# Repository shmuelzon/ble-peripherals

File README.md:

# BLE Peripherals

:exclamation:**Warning**:exclamation: I'm not an EE by any means and I have no
idea what I'm doing! These designs are for reference only and should not be
used.

If you are an EE or am knowledgeable enough to fix my mistakes, a pull
request would be most welcome.

Now that that's out of the way, this repository includes the hardware for
various BLE-based sensors and actuators. Each directory includes a schematic,
PCB layout and a plastic enclosure design for a BLE peripheral.

The software for these designs can be found in my
[cc2640-home-automation](https://github.com/shmuelzon/cc2640-home-automation)
repository.

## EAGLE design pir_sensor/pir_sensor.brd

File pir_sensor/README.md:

# PIR Sensor

This peripheral is a multi-sensor device including a PIR motion sensor, ambient
light sensor, ambient temperature sensor, relative humidity sensor and pressure
sensor.  It also in includes an LED that will turn on when motion was detected.
Depending on the kind of traffic expected where this device will be placed,
consider disabling the LED to conserve battery power.

Battery Type: 1/2 AA (ER14250)

Board configuration for
[cc2640-home-automation](https://github.com/shmuelzon/cc2640-home-automation):
```c
#define Board_LED1                          IOID_4
#define Board_I2C0_SDA0                     IOID_7
#define Board_I2C0_SCL0                     IOID_8
#define Board_MOTION                        IOID_5
#define Board_OPT3001_ADDR                  (0x45)
#define Board_BME280_ADDR                   (0x77)
#define Board_BATT_MAX                      3600
#define Board_BATT_MIN                      1800
```

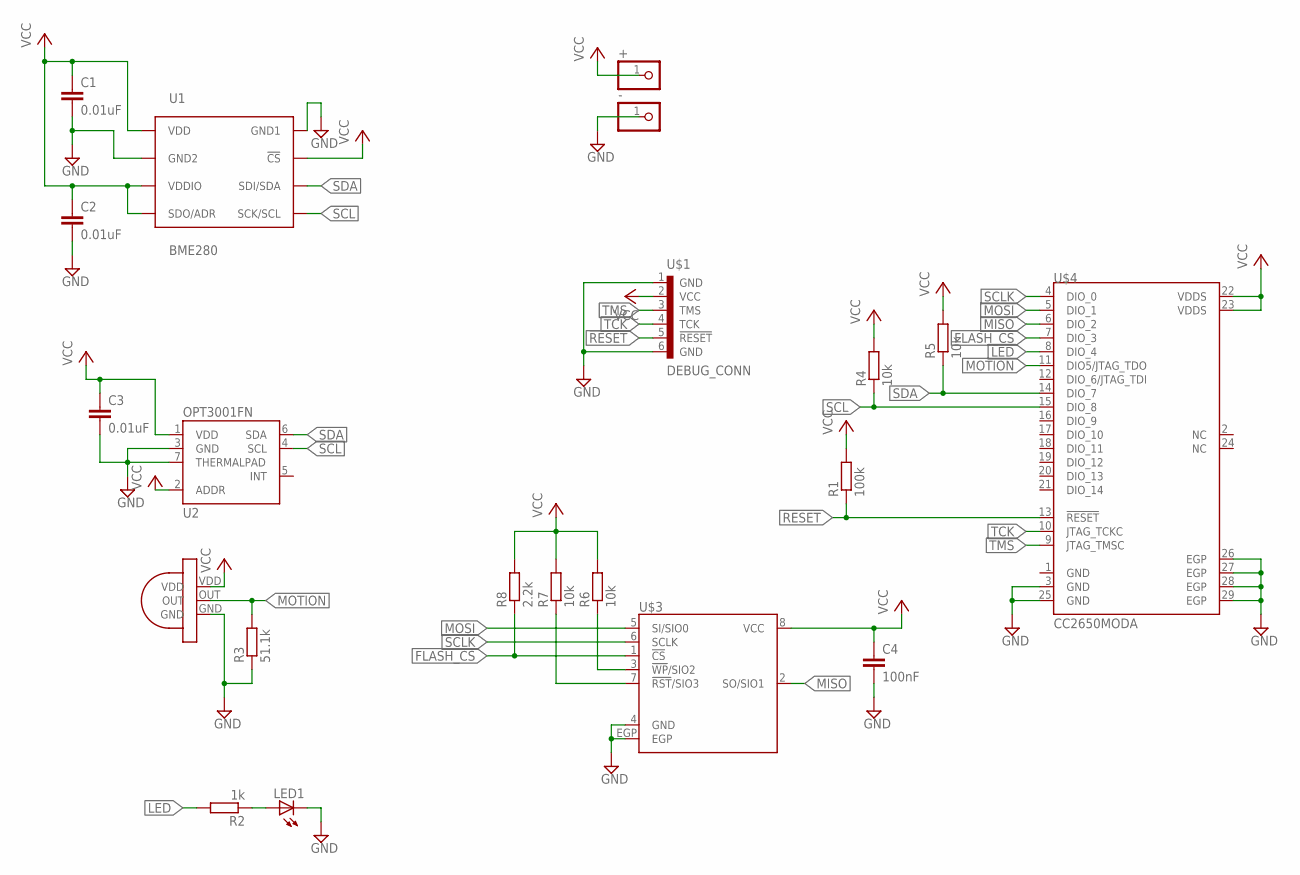
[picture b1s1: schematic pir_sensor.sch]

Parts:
+: PINHD-1X1; 1X01
-: PINHD-1X1; 1X01
C1, C2, C3: 0.01uF; 0402
C4: 100nF; 0402
LED1: LEDCHIP-LED0603; CHIP-LED0603
R1: 100k; 0402
R2: 1k; 0402
R3: 51.1k; 0402
R4, R5, R6, R7: 10k; 0402
R8: 2.2k; 0402
U1: BME280; BME280_LGA
U2: OPT3001FN; TI-USON6-GND-PAD
U$1: DEBUG_CONN
U$2: PAPIR
U$3: MX25R8035FMX25R8035FZUIL0; MX25R8035FZUIL0
U$4: CC2650MODA

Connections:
!RESET: R1.1, U$1.5 (!RESET), U$4.13 (!RESET)
FLASH_CS: R8.1, U$3.1 (!CS), U$4.7 (DIO_3)
GND: -.1, C1.2, C2.2, C3.2, C4.2, LED1.C, R3.1, U1.P$1 (GND1), U1.P$7 (GND2), U2.3 (GND), U2.7 (THERMALPAD), U$1.1 (GND), U$1.6 (GND), U$2.GND, U$3.4 (GND), U$3.EGP, U$4.1 (GND), U$4.3 (GND), U$4.25 (GND), U$4.26 (EGP), U$4.27 (EGP), U$4.28 (EGP), U$4.29 (EGP)
LED: R2.2, U$4.8 (DIO_4)
MISO: U$3.2 (SO/SIO1), U$4.6 (DIO_2)
MOSI: U$3.5 (SI/SIO0), U$4.5 (DIO_1)
MOTION: R3.2, U$2.OUT, U$4.11 (DIO5/JTAG_TDO)
unnamed: R6.1, U$3.3 (!WP!/SIO2)
unnamed: R7.1, U$3.7 (!RST!/SIO3)
unnamed: LED1.A, R2.1
SCL: R4.1, U1.P$4 (SCK/SCL), U2.4 (SCL), U$4.15 (DIO_8)
SCLK: U$3.6 (SCLK), U$4.4 (DIO_0)
SDA: R5.1, U1.P$3 (SDI/SDA), U2.6 (SDA), U$4.14 (DIO_7)
TCK: U$1.4 (TCK), U$4.10 (JTAG_TCKC)
TMS: U$1.3 (TMS), U$4.9 (JTAG_TMSC)
VCC: +.1, C1.1, C2.1, C3.1, C4.1, R1.2, R4.2, R5.2, R6.2, R7.2, R8.2, U1.P$2 (!CS), U1.P$5 (SDO/ADR), U1.P$6 (VDDIO), U1.P$8 (VDD), U2.1 (VDD), U2.2 (ADDR), U$1.2 (VCC), U$2.VDD, U$3.8 (VCC), U$4.22 (VDDS), U$4.23 (VDDS)

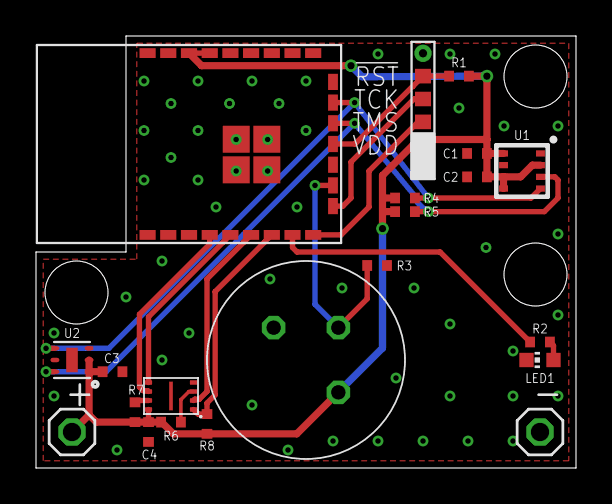
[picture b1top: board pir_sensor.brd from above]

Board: 2 copper layers, 30.0 x 24.0 mm, 21 parts (0 on the bottom side), 16 nets.

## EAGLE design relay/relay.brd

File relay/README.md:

# Relay

This peripheral is a relay with switch sensor. It's to be placed behind the wall
switch where the live wires should be connected to the inner terminals of the
blue block and additional wires should be connected to the green terminals and
the physical switch.

Toggling the switch will toggle the relay.

Battery Type: CR2

Board configuration for
[cc2640-home-automation](https://github.com/shmuelzon/cc2640-home-automation):
```c
#define Board_SWITCH                        IOID_5
#define Board_RELAY_SET                     IOID_7
#define Board_RELAY_RESET                   IOID_8
#define Board_BATT_MAX                      3000
#define Board_BATT_MIN                      2100
```

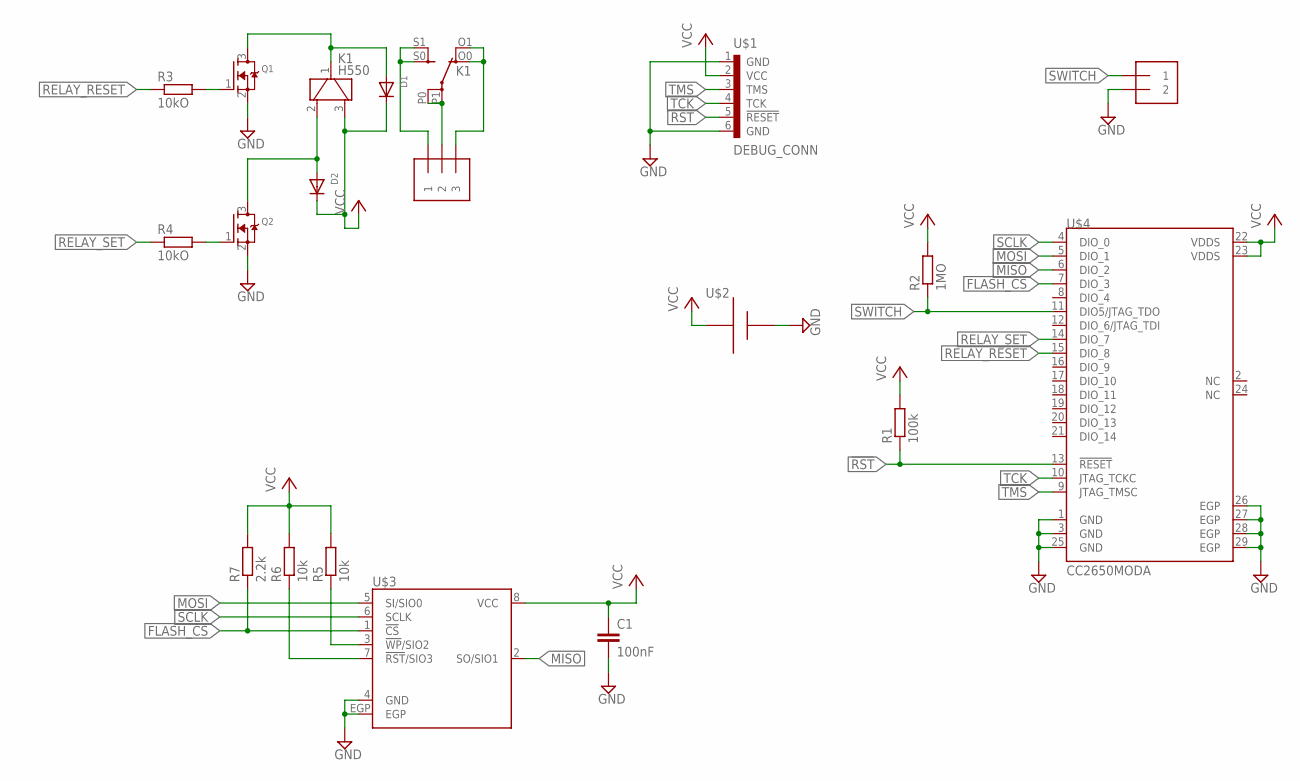
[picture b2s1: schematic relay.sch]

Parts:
C1: 100nF; 0402
D1, D2: DIODESOD-123; SOD-123
J1: 1X3-5MM
J2: 1X2-3.5MM
K1: H550
Q1, Q2: MOSFET-NREFLOW; SOT23
R1: 100k; 0402
R2: 1MO; 0402
R3, R4: 10kO; 0402
R5, R6: 10k; 0402
R7: 2.2k; 0402
U$1: DEBUG_CONN
U$2: CR2_SPRINGS; CR2
U$3: MX25R8035FMX25R8035FZUIL0; MX25R8035FZUIL0
U$4: CC2650MODA

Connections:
!RST: R1.1, U$1.5 (!RESET), U$4.13 (!RESET)
FLASH_CS: R7.1, U$3.1 (!CS), U$4.7 (DIO_3)
GND: C1.2, J2.2, Q1.2 (S), Q2.2 (S), U$1.1 (GND), U$1.6 (GND), U$2.-, U$2.-@1 (-), U$2.-@2 (-), U$2.-@3 (-), U$3.4 (GND), U$3.EGP, U$4.1 (GND), U$4.3 (GND), U$4.25 (GND), U$4.26 (EGP), U$4.27 (EGP), U$4.28 (EGP), U$4.29 (EGP)
MISO: U$3.2 (SO/SIO1), U$4.6 (DIO_2)
MOSI: U$3.5 (SI/SIO0), U$4.5 (DIO_1)
unnamed: J1.1, K1.S0 (S), K1.S1 (S)
unnamed: J1.3, K1.O0 (O), K1.O1 (O)
unnamed: D1.A, K1.1, Q1.3 (D)
unnamed: D2.A, K1.2, Q2.3 (D)
unnamed: Q1.1 (G), R3.2
unnamed: Q2.1 (G), R4.2
unnamed: J1.2, K1.P0, K1.P1
unnamed: R5.1, U$3.3 (!WP!/SIO2)
unnamed: R6.1, U$3.7 (!RST!/SIO3)
RELAY_RESET: R3.1, U$4.15 (DIO_8)
RELAY_SET: R4.1, U$4.14 (DIO_7)
SCLK: U$3.6 (SCLK), U$4.4 (DIO_0)
SWITCH: J2.1, R2.1, U$4.11 (DIO5/JTAG_TDO)
TCK: U$1.4 (TCK), U$4.10 (JTAG_TCKC)
TMS: U$1.3 (TMS), U$4.9 (JTAG_TMSC)
VCC: C1.1, D1.C, D2.C, K1.3, R1.2, R2.2, R5.2, R6.2, R7.2, U$1.2 (VCC), U$2.+, U$2.+@1 (+), U$2.+@2 (+), U$2.+@3 (+), U$3.8 (VCC), U$4.22 (VDDS), U$4.23 (VDDS)

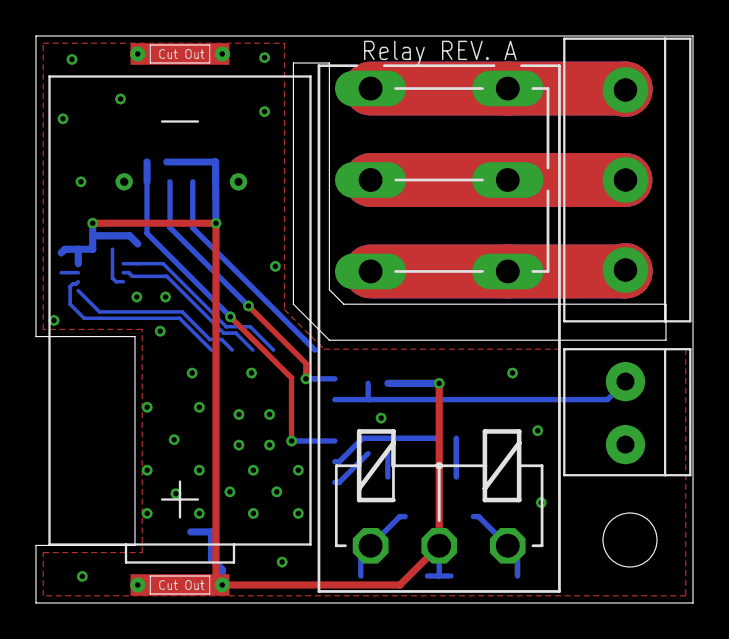
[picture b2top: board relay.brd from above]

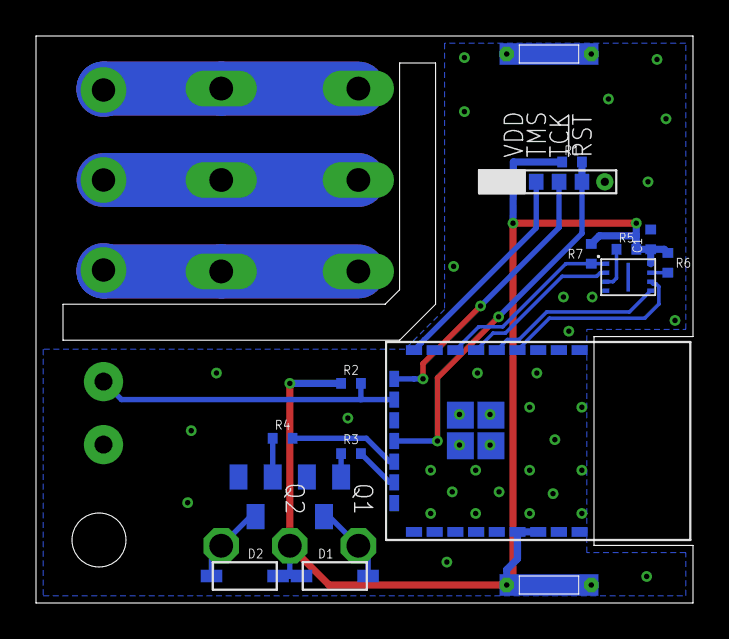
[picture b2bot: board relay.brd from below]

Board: 2 copper layers, 36.5 x 31.5 mm, 19 parts (15 on the bottom side), 21 nets.

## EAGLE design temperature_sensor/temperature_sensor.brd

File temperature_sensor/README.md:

# Temperature Sensor

This peripheral is a temperature sensor based on a thermistor. It can be used to
measure the temperature at various locations, e.g. the thermostat of a water
heater / boiler.

Battery Type: 1/2 AA (ER14250)

Board configuration for
[cc2640-home-automation](https://github.com/shmuelzon/cc2640-home-automation):
```c
#define Board_THERMISTOR_POWER              IOID_0
#define Board_THERMISTOR                    Board_ADC7
#define Board_BATT_MAX                      3600
#define Board_BATT_MIN                      1800
```

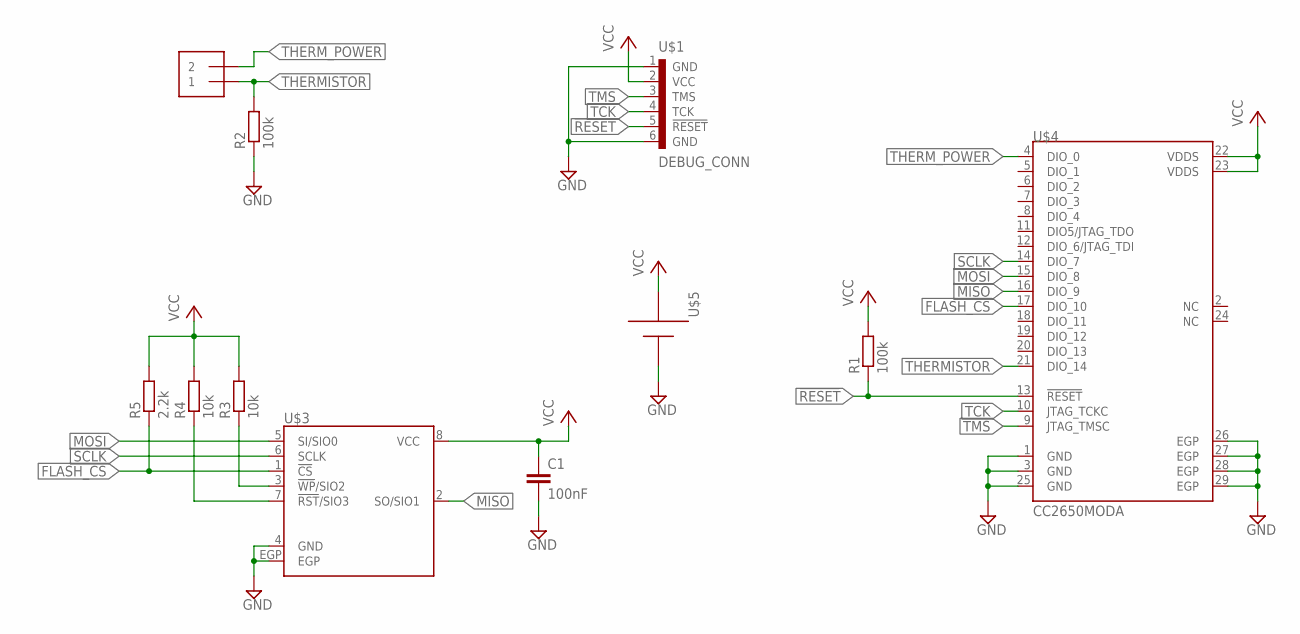
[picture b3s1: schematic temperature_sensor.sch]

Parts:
C1: 100nF; 0402
J2: 1X2-3.5MM
R1, R2: 100k; 0402
R3, R4: 10k; 0402
R5: 2.2k; 0402
U$1: DEBUG_CONN
U$3: MX25R8035FMX25R8035FZUIL0; MX25R8035FZUIL0
U$4: CC2650MODA
U$5: CR2_SPRINGS; CR2

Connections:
!RESET: R1.1, U$1.5 (!RESET), U$4.13 (!RESET)
FLASH_CS: R5.1, U$3.1 (!CS), U$4.17 (DIO_10)
GND: C1.2, R2.1, U$1.1 (GND), U$1.6 (GND), U$3.4 (GND), U$3.EGP, U$4.1 (GND), U$4.3 (GND), U$4.25 (GND), U$4.26 (EGP), U$4.27 (EGP), U$4.28 (EGP), U$4.29 (EGP), U$5.-, U$5.-@1 (-), U$5.-@2 (-), U$5.-@3 (-)
MISO: U$3.2 (SO/SIO1), U$4.16 (DIO_9)
MOSI: U$3.5 (SI/SIO0), U$4.15 (DIO_8)
unnamed: R3.1, U$3.3 (!WP!/SIO2)
unnamed: R4.1, U$3.7 (!RST!/SIO3)
SCLK: U$3.6 (SCLK), U$4.14 (DIO_7)
TCK: U$1.4 (TCK), U$4.10 (JTAG_TCKC)
THERMISTOR: J2.1, R2.2, U$4.21 (DIO_14)
THERM_POWER: J2.2, U$4.4 (DIO_0)
TMS: U$1.3 (TMS), U$4.9 (JTAG_TMSC)
VCC: C1.1, R1.2, R3.2, R4.2, R5.2, U$1.2 (VCC), U$3.8 (VCC), U$4.22 (VDDS), U$4.23 (VDDS), U$5.+, U$5.+@1 (+), U$5.+@2 (+), U$5.+@3 (+)

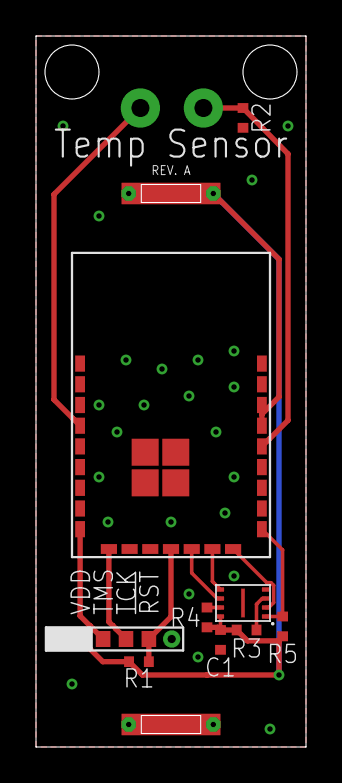
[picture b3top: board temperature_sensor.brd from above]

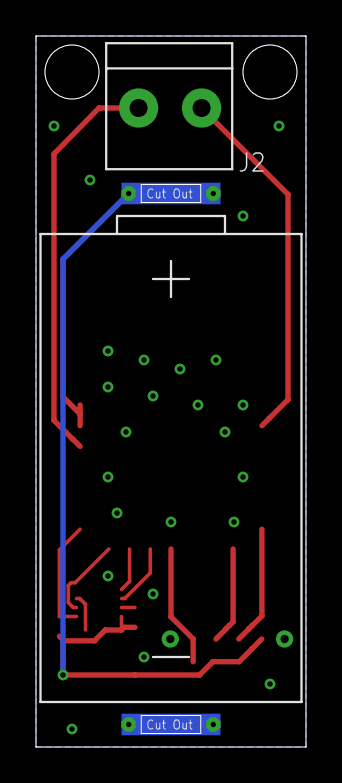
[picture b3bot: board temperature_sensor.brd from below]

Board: 2 copper layers, 15.0 x 39.5 mm, 11 parts (2 on the bottom side), 13 nets.

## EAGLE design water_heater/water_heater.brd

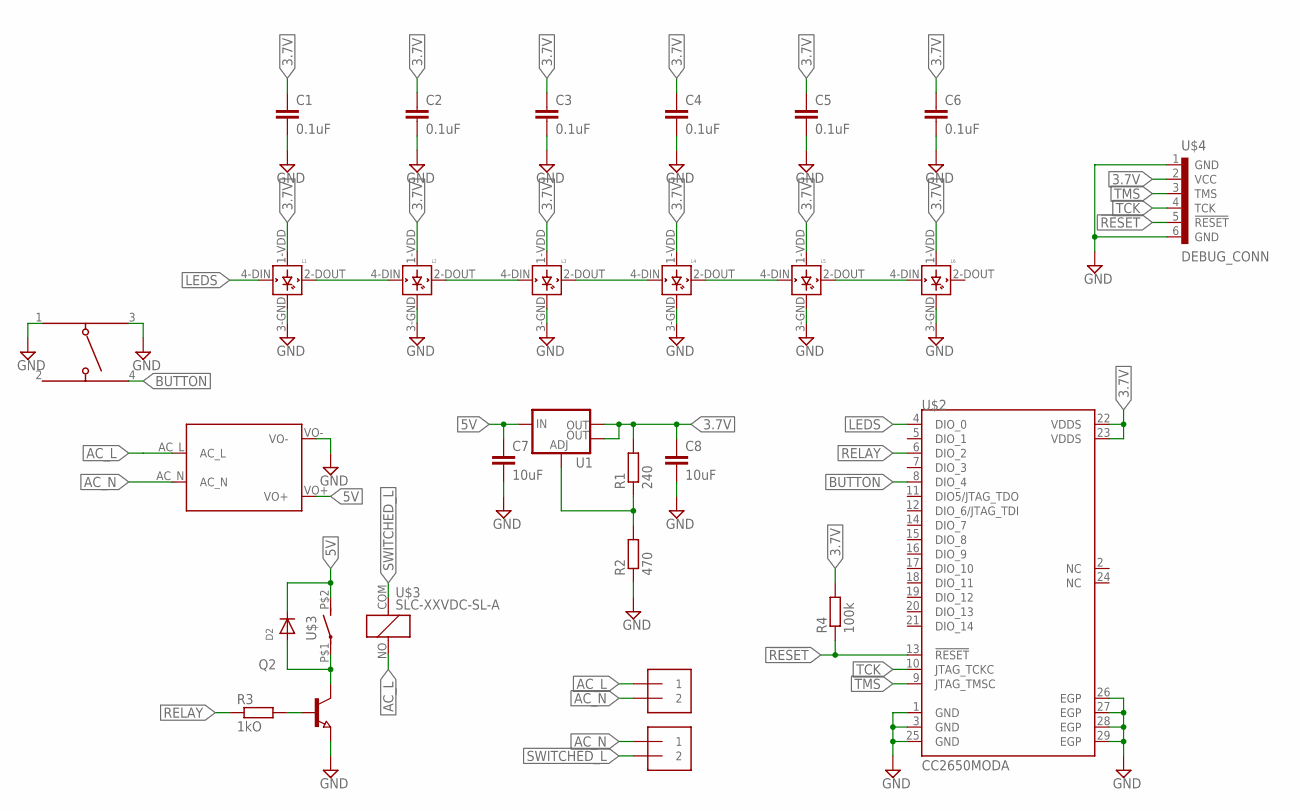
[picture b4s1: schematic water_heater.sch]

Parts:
C1, C2, C3, C4, C5, C6: 0.1uF; 0402
C7, C8: 10uF; 0402
D2: DIODESOD-123; SOD-123
L1, L2, L3, L4, L5, L6: WS2812B
Q2: NPN-TRANSISTOR_SOT23; SOT23
R1: 240; 0402
R2: 470; 0402
R3: 1kO; 0402
R4: 100k; 0402
U1: V_REG_LM1117SOT223; SOT223
U$1: HLK-PM01
U$2: CC2650MODA
U$3: SLC-XXVDC-SL-A; SLC-1_FORM_A
U$4: DEBUG_CONN
U$5: CTS222AM
U$8, U$9: 1X2-5MM-RIGHT

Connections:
3.7V: C1.1, C2.1, C3.1, C4.1, C5.1, C6.1, C8.1, L1.1-VDD (VDD), L2.1-VDD (VDD), L3.1-VDD (VDD), L4.1-VDD (VDD), L5.1-VDD (VDD), L6.1-VDD (VDD), R1.2, R4.2, U1.2 (OUT), U1.4 (OUT), U$2.22 (VDDS), U$2.23 (VDDS), U$4.2 (VCC)
5V: C7.1, D2.C, U1.3 (IN), U$1.VO+, U$3.P$2 (S)
!RESET: R4.1, U$2.13 (!RESET), U$4.5 (!RESET)
AC_L: U$1.AC_L, U$3.NO (2), U$8.1
AC_N: U$1.AC_N, U$8.2, U$9.1
BUTTON: U$2.8 (DIO_4), U$5.4
GND: C1.2, C2.2, C3.2, C4.2, C5.2, C6.2, C7.2, C8.2, L1.3-GND (GND), L2.3-GND (GND), L3.3-GND (GND), L4.3-GND (GND), L5.3-GND (GND), L6.3-GND (GND), Q2.2 (E), R2.1, U$1.VO-, U$2.1 (GND), U$2.3 (GND), U$2.25 (GND), U$2.26 (EGP), U$2.27 (EGP), U$2.28 (EGP), U$2.29 (EGP), U$4.1 (GND), U$4.6 (GND), U$5.1, U$5.3
LEDS: L1.4-DIN (DIN), U$2.4 (DIO_0)
unnamed: Q2.1 (B), R3.2
unnamed: L4.2-DOUT (DOUT), L5.4-DIN (DIN)
unnamed: L1.2-DOUT (DOUT), L2.4-DIN (DIN)
unnamed: D2.A, Q2.3 (C), U$3.P$1
unnamed: L2.2-DOUT (DOUT), L3.4-DIN (DIN)
unnamed: L3.2-DOUT (DOUT), L4.4-DIN (DIN)
unnamed: L5.2-DOUT (DOUT), L6.4-DIN (DIN)
unnamed: R1.1, R2.2, U1.1 (ADJ)
RELAY: R3.1, U$2.6 (DIO_2)
SWITCHED_L: U$3.COM (1), U$9.2
TCK: U$2.10 (JTAG_TCKC), U$4.4 (TCK)
TMS: U$2.9 (JTAG_TMSC), U$4.3 (TMS)

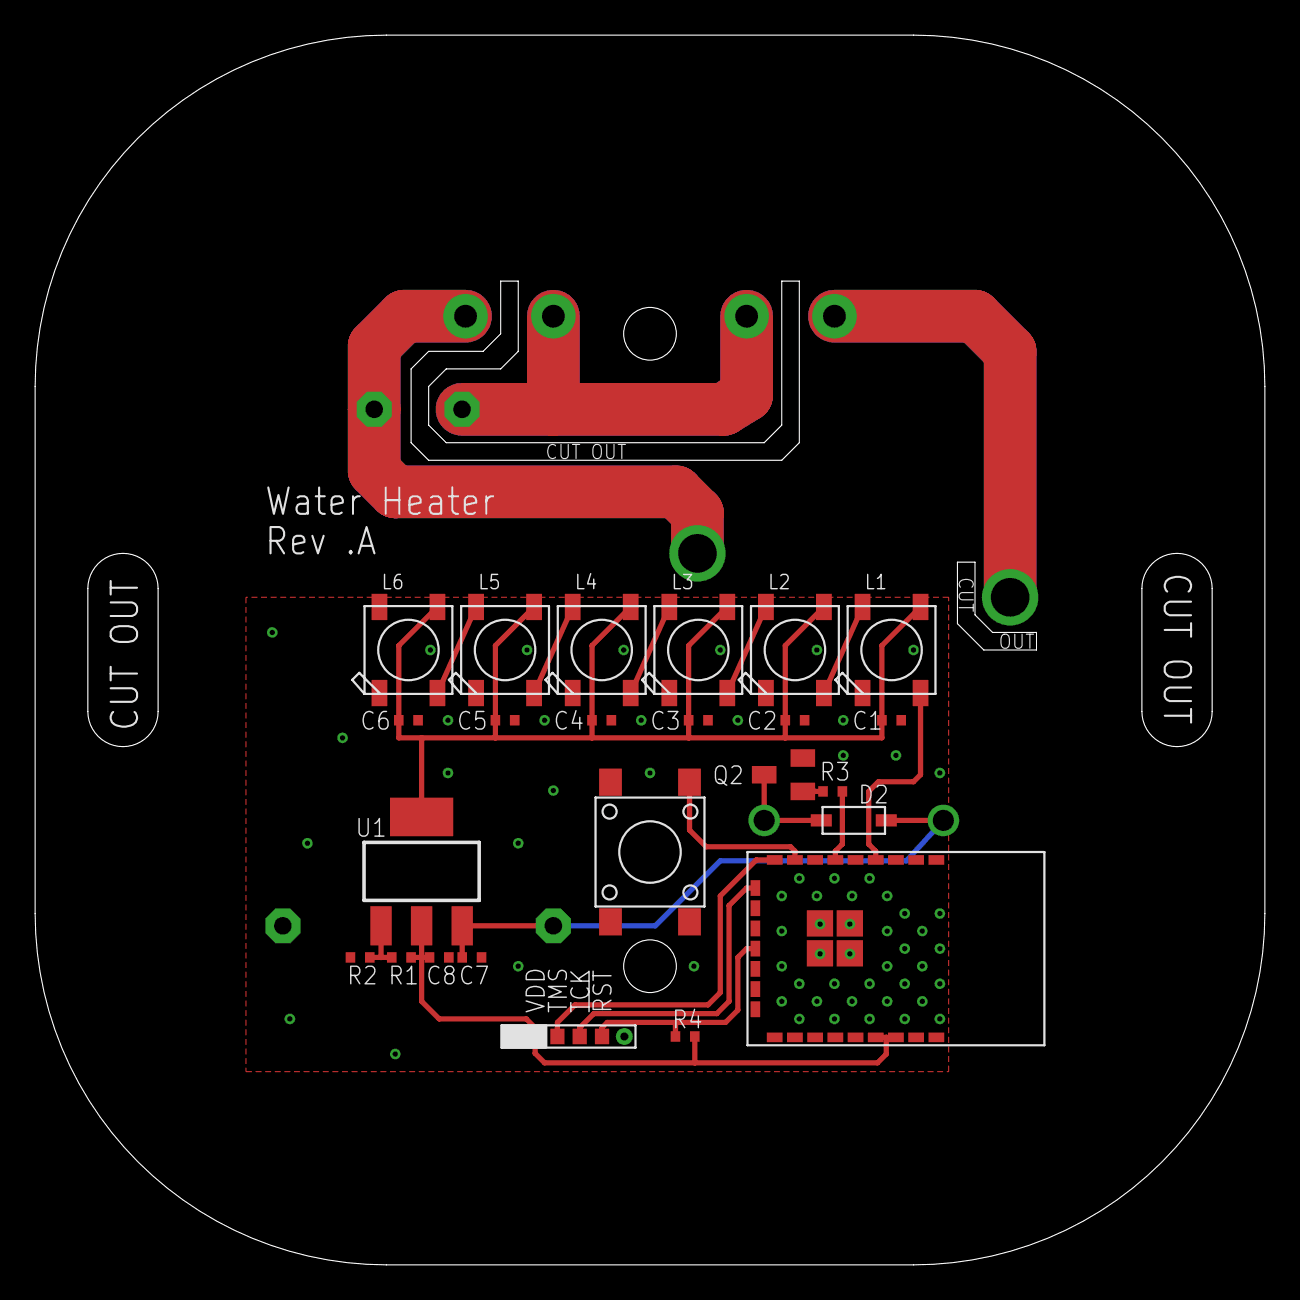
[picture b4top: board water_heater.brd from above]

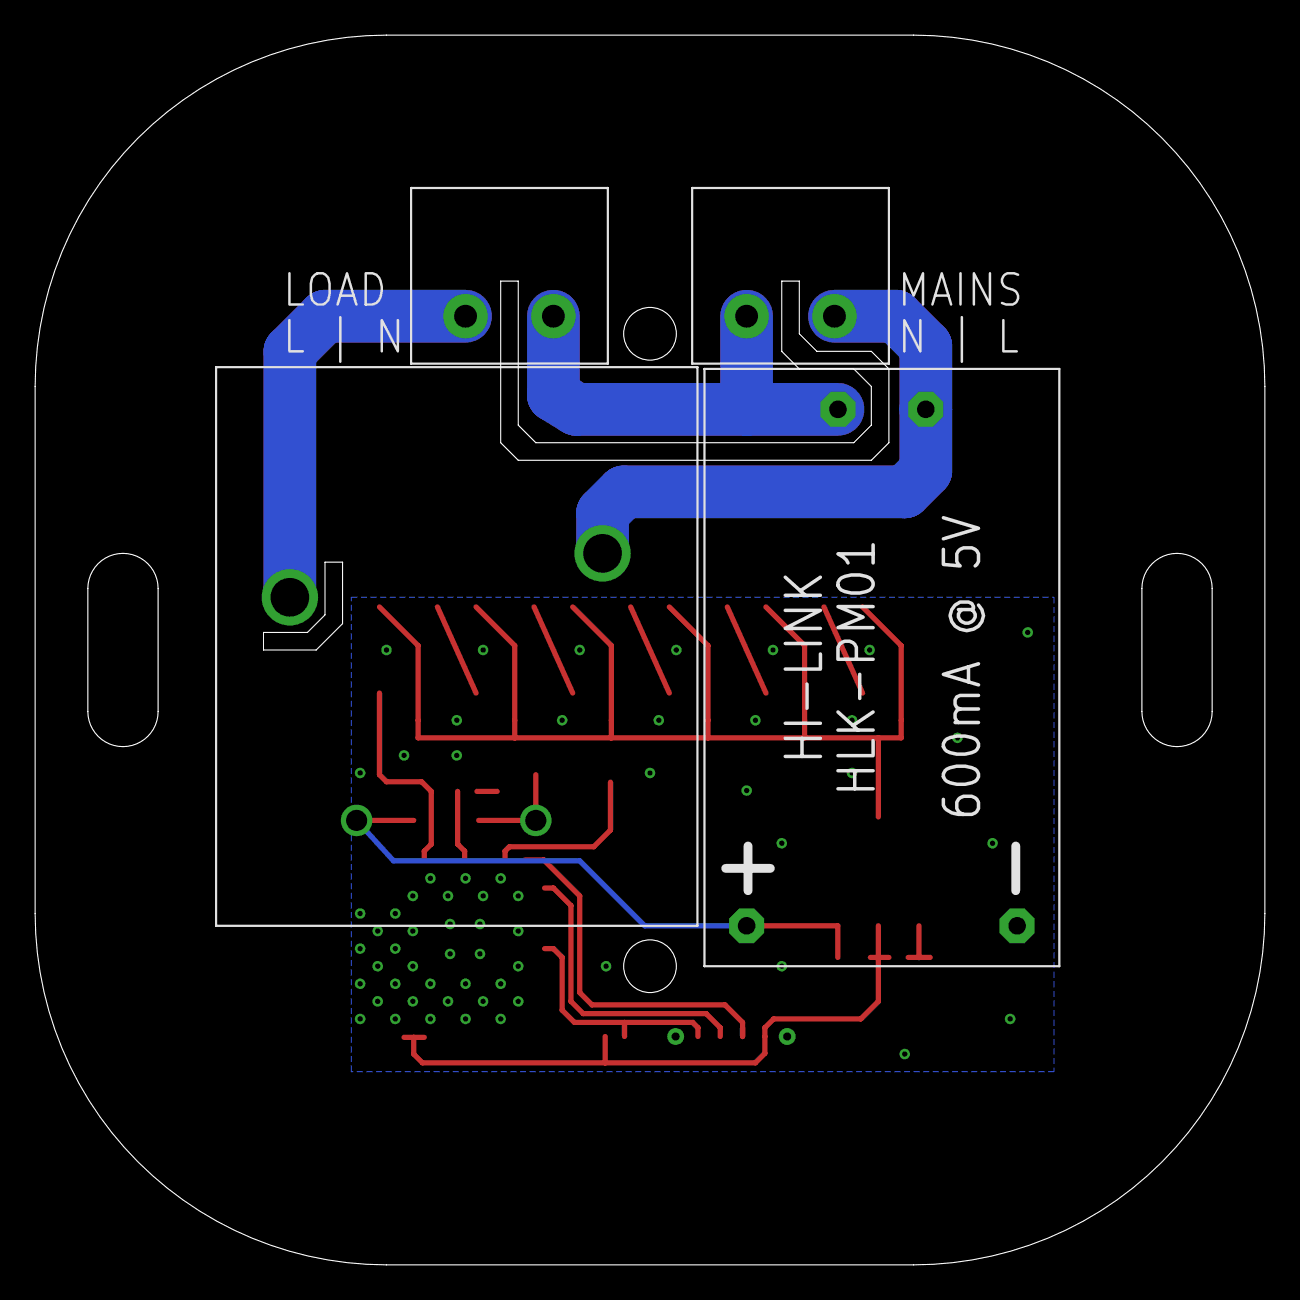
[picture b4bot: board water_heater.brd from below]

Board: 2 copper layers, 70.0 x 70.0 mm, 28 parts (4 on the bottom side), 20 nets.

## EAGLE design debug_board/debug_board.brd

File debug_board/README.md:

# Debug Board

This board is to connect the XDS100v3 (or similar) to the BLE peripherals in
this repository. The pogo pins, used to create contact with the BLE PCBs, should
be soldered in a manner that the out-most pins are a bit lower than the rest.
This should allow easier aligning of the pins with the BLE peripheral PCB.

The pogo pins must be soldered straight and can be easily done by stacking a few
of these PCBs together before soldering.

External power can also be applied using the additional pin headers instead of
relying on the peripheral's power source (which should be disconnected if not
used).

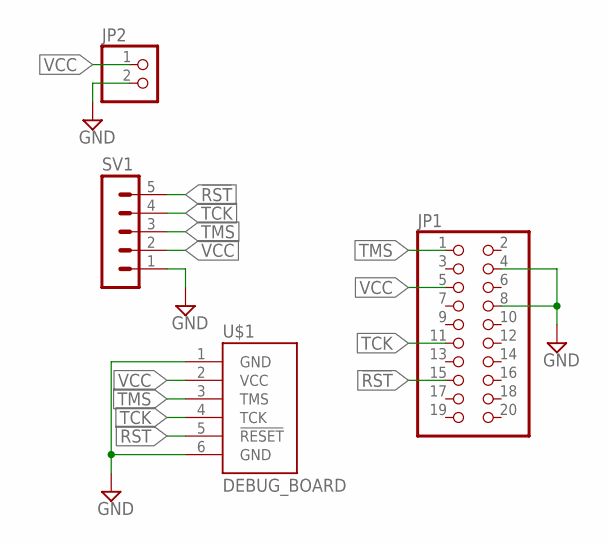
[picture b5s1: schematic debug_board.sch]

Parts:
JP1: PINHD-2X10; 2X10
JP2: PINHD-1X2; 1X02
SV1: MA05-1
U$1: DEBUG_BOARD

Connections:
!RST: JP1.15, SV1.5, U$1.5 (!RESET)
GND: JP1.4, JP1.8, JP2.2, SV1.1, U$1.1 (GND), U$1.6 (GND)
TCK: JP1.11, SV1.4, U$1.4 (TCK)
TMS: JP1.1, SV1.3, U$1.3 (TMS)
VCC: JP1.5, JP2.1, SV1.2, U$1.2 (VCC)

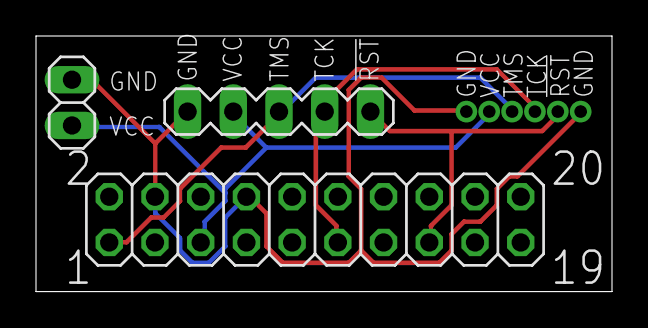
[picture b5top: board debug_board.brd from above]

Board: 2 copper layers, 32.0 x 14.2 mm, 4 parts (0 on the bottom side), 5 nets.

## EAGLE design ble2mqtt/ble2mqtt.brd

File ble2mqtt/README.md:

# BLE2MQTT

This PCB is for the ESP32-WROOM-32 module arranged to be in line with a USB wall
wart. It includes a USB-to-Serial controller for loadind the initial software
from [esp32-ble2mqtt](https://github.com/shmuelzon/esp32-ble2mqtt).

The USB header portion is meant to be broken off and soldered vertically in the
appropriate slot.

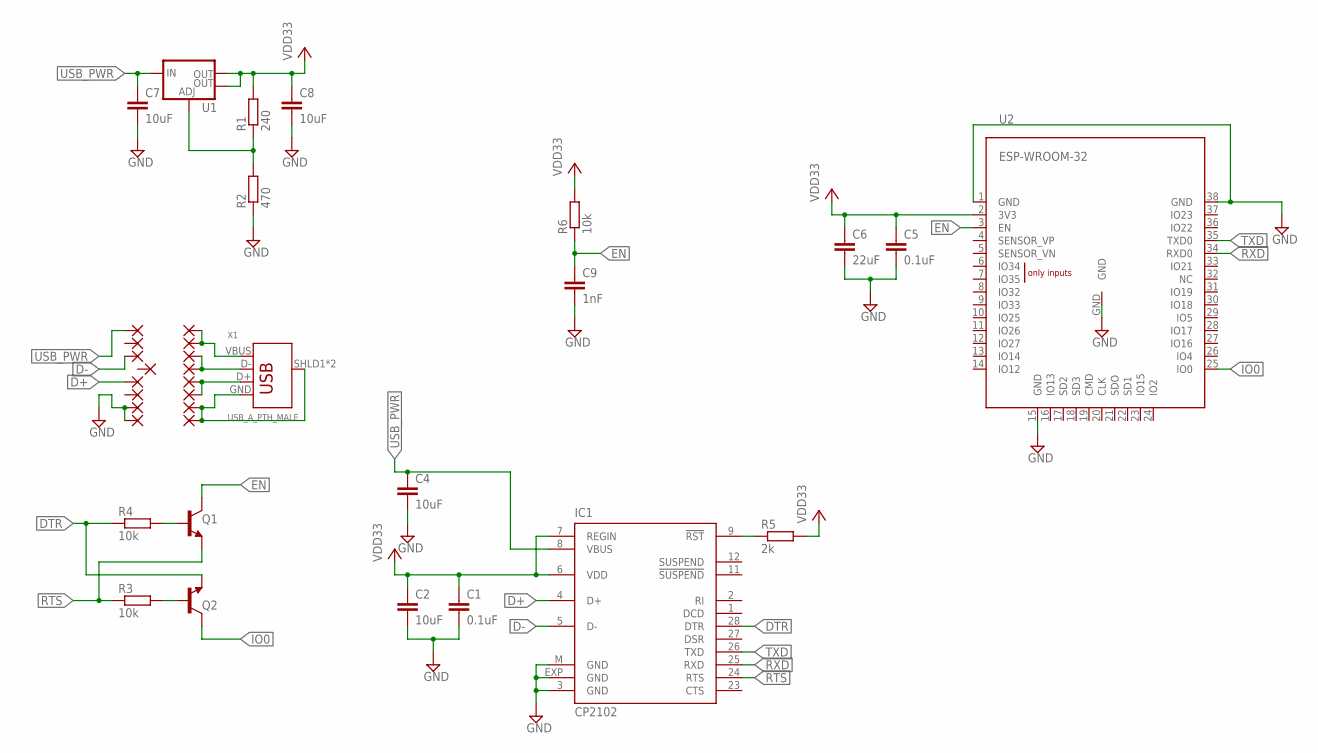
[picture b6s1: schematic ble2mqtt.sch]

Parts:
C1, C5: 0.1uF; 0402
C2, C4, C7, C8: 10uF; 0402
C6: 22uF; 0402
C9: 1nF; 0402
IC1: CP2102; MLP28
PAD1, PAD2, PAD3, PAD4, PAD5, PAD6, PAD7, PAD8, PAD9, PAD10, PAD11, PAD12, PAD13, PAD14, PAD15, PAD16: WIREPADSMD1,27-254; SMD1,27-2,54
Q1, Q2: TRANS_NPN-MMBT2222AL; SOT23-3
R1: 240; 0402
R2: 470; 0402
R3, R4, R6: 10k; 0402
R5: 2k; 0402
U1: V_REG_LM1117SOT223; SOT223
U2: ESP-WROOM-32
X1: USB_A_PTH_MALE; USB-A-H

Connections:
D+: IC1.4 (D+), PAD13.1
D-: IC1.5 (D-), PAD11.1
DTR: IC1.28 (DTR), Q2.2 (E), R4.1
EN: C9.1, Q1.3 (C), R6.1, U2.3 (EN)
GND: C1.2, C2.2, C4.2, C5.2, C6.2, C7.2, C8.2, C9.2, IC1.3 (GND), IC1.EXP (GND), IC1.M (GND), PAD15.1, PAD16.1, R2.1, U2.1 (GND), U2.15 (GND), U2.38 (GND), U2.GND
GND2: PAD7.1, PAD8.1, X1.GND, X1.SHLD1 (SHIELD), X1.SHLD2 (SHIELD)
IO0: Q2.3 (C), U2.25 (IO0)
unnamed: IC1.9 (!RST), R5.1
unnamed: Q2.1 (B), R3.2
unnamed: PAD1.1, PAD2.1, X1.VBUS
unnamed: PAD3.1, PAD4.1, X1.D-
unnamed: Q1.1 (B), R4.2
unnamed: PAD5.1, PAD6.1, X1.D+
unnamed: R1.1, R2.2, U1.1 (ADJ)
RTS: IC1.24 (RTS), Q1.2 (E), R3.1
RXD: IC1.25 (RXD), U2.34 (RXD0)
TXD: IC1.26 (TXD), U2.35 (TXD0)
USB_PWR: C4.1, C7.1, IC1.8 (VBUS), PAD9.1, U1.3 (IN)
VCC: C1.1, C2.1, C5.1, C6.1, C8.1, IC1.6 (VDD), IC1.7 (REGIN), R1.2, R5.2, R6.2, U1.2 (OUT), U1.4 (OUT), U2.2 (3V3)

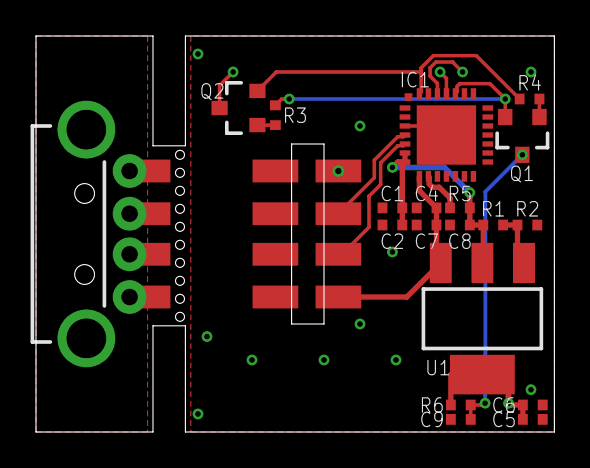
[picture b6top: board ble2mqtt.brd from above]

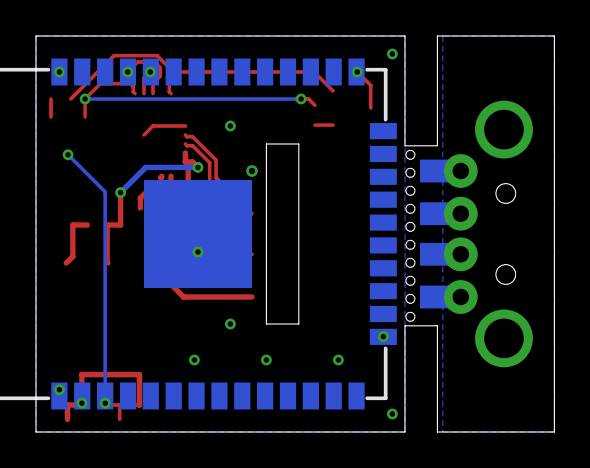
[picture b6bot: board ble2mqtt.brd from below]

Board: 2 copper layers, 28.8 x 22.0 mm, 36 parts (5 on the bottom side), 19 nets.

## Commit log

2019-02-13 Initial empty commit
2019-02-13 Initial release

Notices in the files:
parts and their libraries:
SparkFun-IC-Power: Licensing: Creative Commons ShareAlike 4.0 International - https://creativecommons.org/licenses/by-sa/4.0
